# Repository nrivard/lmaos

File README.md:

# LmaOS

LmaOS is a 65C02 system kernal designed primarily for the n8 Bit Microcomputer, a homebrew computer.
If you are looking for the hardware this is designed to run on, check out the [n8 Bit Microcomputer](https://github.com/nrivard/n8-bit).

## Getting Started

To build LmaOS, you will need `make` and the [CC65 suite](https://cc65.github.io) or my unreleased 65C02 IDE for macOS, System On Chip (how did you get this? It's unreleased!)

From the root directory, run `make`:

```bash
$ make
/usr/local/bin/cl65 -t none -C LmaOS.65c02/memorymap.cfg --asm-include-dir LmaOS.65c02/include -l lmaos.rom.listing -vm --mapfile lmaos.rom.map --cpu 65C02 -o ./lmaos.rom  LmaOS.65c02/src/main.asm
```

To install LmaOS on an EEPROM for use in your n8 Bit Microcomputer, you will need [minipro](https://gitlab.com/DavidGriffith/minipro) and a TL866II Plus programmer.
Again, from the root directory, run `make install`:

```bash
$ make install
minipro -p AT28C256 -w lmaos.rom
Found TL866II+ 04.2.122 (0x27a)
Erasing... 0.02Sec OK
Protect off...OK
Writing Code...  6.78Sec  OK
Reading Code...  0.48Sec  OK
```

## Conventions

LmaOS has a few conventions to consider.
First, LmaOS uses 16 bit pseudo-registers for passing data between system subroutines: `r0` through `r7` (see `zeropage.inc`.)
These registers should be considered volatile and if you use them in your program and call system functions, they could be mutated.

Second, register values at this time should _also_ be considered volatile (with the exception of interrupt handling) so if you care about these values, push them onto the stack or store them elsewhere before calling system routines.
Exactly what is used should be in the documentation for each subroutine.

Lastly, some programming conventions are:

* constants and volatile storage (`.bss`) are in an `.inc` file
* code and non-volatile storage (`RODATA`) are in an `.asm` file
* Border-line excessive use of local labels in subroutines (prefixed with `@`).
Not all of these local labels are actually used as labels (in the assembler sense) but instead are intended as self-documenting organizational tools.

For example, many routines will have an immediate local label named `@Preamble` on entry to a subroutine and almost all have a `@Done` before `RTS` even when no branches jump to it.
It's not strictly necessary, you could jump to the top-level label if necessary, but I like to organize the code this way.

```asm
RandomSubroutine:
@Preamble:
    PHA
    PHX
@GenerateRandomNumber:
    ...
@Done:
    PLX
    PLA
    RTS
```

## Hardware Support

LmaOS was written primarily for the n8 Bit Microcomputer but likely needs customization, which could make it suitable for other designs as well.

### System Globals

System globals that are used throughout LmaOS are declared in `system.inc`.
This includes the system clock speed constant (needed for precise timing) and declarations for the n8 Bus ports` addresses.
These follow the default memory mapping of the n8 Bit Microcomputer but you can customize them here if you changed that.

Normally, there should be no need to customize the system uptime interrupt interval unless you need higher accuracy, the routine is taking too much time for your uses, or you want to use it instead as more of a VSYNC timer for consistent frames.

### Zeropage

LmaOS has carved out some of zeropage for particular uses.
This includes the pseudo-registers (which are also for your program use), system uptime, the global interrupt vector, and more.
See `zeropage.inc` for details on what is used and what is available for your own program use.

### Expansion Ports

When you add, remove, or change the order of your installed expansion cards (or your system doesn't have any), you will have to recompile LmaOS.

First you will have to update the base address for system utilities to work.
For example, if you've installed a VIA, in `via.inc` you'll want `VIA_BASE` to point to the correct base memory address.
If you're using a n8 Bit Micrcomputer, you can just use the global n8 Bus port constant:

```asm
VIA_BASE := N8BUS_PORT2
```

There is system support for an ACIA, VIA, and 1602 style LCDs.
If you are using different hardware for these, you may be able to just adapt what is provided for your purposes.

## System utilities

LmaOS provides some system support for the ACIA, VIA, and 1602 style LCDS as well as some built-in strings utilities.

### VIA

The VIA provides system timer support from Timer 1.
If you want to take advantage of system uptime and jiffies, do not use Timer 1 and do not disable interrupts.
By default, both I/O ports are configured for output.
See `via.inc` and `via.asm` for more details.

### ACIA

Basic ACIA functions are provided: `ACIAGetByte`, `ACIASendByte`, and `ACIASendString`.
All of these routines are synchronous, meaning they could lock up the system if there is no response from a connected system.
A fully working interrupt driven ACIA implementation was written if you want to comb the commit history but it was way too complicated for realworld use.
See `acia.inc` and `acia.asm` for more details.

The XModem receive subroutine used by Monitaur's `tx` command is provided for program use as well: `XModemReceive`.
See `xmodem.inc` and `xmodem.asm` for more details.

### Strings

Some C lib like string utilities are provided including: `StringLength`, `StringCompareN`, `StringCompare`, `StringCopy`, `HexStringToWord`, `ByteToHexString`, and `NibbleToHexString`. See `strings.asm` for more details.

### Pseudoinstructions

Pseudoinstructions are provided via macros.
These can simplify common but rote tasks and make your code more readable but be careful when you use them.
They may not always do what you think they do!
You can discover them in `pseudoinstructions.inc`.

## Monitaur

At bootup, LmaOS boots into its monitor, called Monitaur. 
Monitaur provides 4 basic commands: `rd`, `wr`, `tx`, and `ex`.
All numeric values in Monitaur are in hexadecimal (written as `$<number>` throughout this document).
Where noted, a `word` is 16 bits and a `byte` is 8 bits.

In general, Monitaur parses all values as a word but a command may ignore the upper nibble if it expects a byte.
See `monitaur.inc` and `monitaur.asm` for more details.

### Reading memory

The `rd` command allows you to read system memory. You provide an address (word) and, optionally, a length (byte).

```
>rd 0400
A9
```

By default, if you don't specify a length, it defaults to `$1`.
To read blocks of memory, you can provide a length.

```
>rd 1000 10
AB 11 FE 6F D9 DB 2D FD 26 F4 82 FE F1 A6 95 8B
```
 
Monitaur will print `$10` values per line.
Length is provided as a byte and so the maximum value you can read is `$100`. 
To read the full `$100` values, because of how the monitor is written, you must provide the length as `$0` not `$FF`.

```
>rd 1000 0
AB 11 FE 6F D9 DB 2D FD 26 F4 82 FE F1 A6 95 8B 
25 33 49 6F 8D C0 03 3C EA D7 9F F6 0F CB ED E1 
D3 73 F8 4C C7 BA 7F B7 EB 53 5B 5E DD BC FA C1 
63 B7 E8 8F 29 91 A2 5C 13 1B E7 F7 73 72 73 BE 
B1 91 14 FC DA 5A 9F E7 D7 8F CF 7F 82 6E DB F7 
3F E7 AA 9B 1E A8 61 D9 4B 5D FF 9C 58 B7 74 BA 
7C 3D 26 FE 73 77 9F 1E 9B 5F 70 BE 75 AB 37 A3 
45 E4 B5 28 E0 E3 3D C4 D5 F1 9F 60 8F 9C 7E A3 
EE 9E F9 3E EA DF 27 EF F3 55 C8 E8 6D 1A F7 BE 
DA B3 26 C6 FE EE FD 6F 67 58 A7 79 F5 58 B5 4D 
B5 36 FA A8 66 9D B5 91 FF FA 8B B7 FF BF D3 39 
4F E7 F3 BF 39 BF D7 D0 F5 7F FF 9B E8 6C 93 9C 
2C 5C DE DD DD B3 75 7F 3E DE 7B C8 4F 4F 65 EA 
7F E4 5F 51 BF 70 B1 1B FF FF E6 D2 EA F9 77 BD 
93 EE EE 37 51 0F 8B 9E 8F E4 F9 B7 AF CE B7 BB 
FF 13 BE F9 EF FA FF EE ED 27 67 E0 5F BD 11 83
```

### Writing memory

The `wr` command allows you to write to system memory (provided it is writeable!)
You provide an address (word) and a value (byte) to be written.

```
>wr 1000 A5
```

Values can only be written 1 at a time through this command.
There is no feedback if a write fails because you tried to write to an address that is read-only (like ROM).
If you need to know if your `wr` succeeded, send a `rd` command with the address and verify the value.

### Transferring data

The `tx` command allows you to transfer data from the connected system to the n8 Bit Microcomputer.
You provide an address (word) to start writing the data.

```
>tx 0400
Waiting for XModem transfer...
```

When prompted, your connected system can send a file via the XModem Checksum (not CRC) protocol.
When the transfer is completed or canceled, you will be returned to Monitaur.
The `tx` command will write _all_ data sent, including EOF padding (`$1A` from the serial app I use), it makes no attempt to discover the true EOF.

### Executing programs

The `ex` command executes code starting at the provided address (word).

```
>ex 0400
```

`ex` does this by jumping to the provided address as a subroutine (`JSR <address>`).
Your program is expected to know where it will be written (because you likely used `tx` and provided that address!)
When your program is done executing, calling `RTS` will return you to Monitaur.

_Note: You should always start writing your program after address $0400, as there are two `$80` length buffers needed by Monitaur (for command storage) and `tx` (for packet storage) as well as some other bookkeeping when transferring data._

## Writing Programs

The point of the n8 Bit Microcomputer and LmaOS is to write programs and see them come to life!
Take a look at the following guidelines and the included example programs.

### The Basics

To write programs for the n8 Bit Microcomputer (and LmaOS), copy any of the relevant include (`.inc`) files for your use.
Set an origin for your program (I like `$0400`) as there is no built-in relocation scheme yet.
If your program just performs a small task, remember to call `RTS` to return to Monitaur.
If you never need to return to Monitaur, don't worry about it!

_Note: When you transfer your program, the transfer location must match the origin!_

Here's a very simple program that will write an alternating pattern to the VIA's 2 I/O ports:

```asm
.org $0400

Main:
    LDA #$AA
    STA VIA_BASE+PORT_A
    STA VIA_BASE+PORT_B
    RTS

.include "via.inc"
```

Then transfer the program using Monitaur and execute it:

```
LmaOS v1.0
Unauthorized access of this N8 Bit Microcomputer will result in prosecution!
>tx 0400
Waiting for XModem transfer...
Transmission successful.
>ex 0400
>
```

If you need to execute system provided (ROM) subroutines, copy `lmaos.inc` into your project.
This file is not actually used by LmaOS; instead it is just a listing of the addresses of externally available system functionality.

`lmaos.inc` is generated each time you run `make` on LmaOS.
This means you will have to copy this file to your program's project and reassemble each time you update your system's ROM.
You can also directly `include` this file (and all the other system utitilies) as the example programs do in this repo.
See the `Makefile` of the examples for how to do this.

```asm
.org $0400

Main:
@ClearScreen:
    LDA #(LCD_INSTR_CLEAR)
    JSR LCDSendInstruction
@PrintMsg:
    LDA #<WelcomeMsg
    LDX #>WelcomeMsg
    JSR LCDPrintString
@Done:
    RTS

WelcomeMsg: .asciiz "Welcome to LmaOS!"

.include "lmaos.inc"
```

### Injecting Interrupt Handlers

If you add new hardware support or want to piggyback on the system timer interrupt, LmaOS provides a way to inject your own interrupt handlers.

First, you will need to overwrite `InterruptVector` (we will write `CustomInterrupt` in the next step):

```asm
SystemInterrupt: .res 2                         ; we'll store the original vector here

InjectInterrupt:
    SEI                                         ; turn off interrupts. we don't want them firing when we overwrite this
    COPY16 InterruptVector, SystemInterrupt     ; store original vector
    COPYADDR CustomInterrupt, InterruptVector   ; inject our interrupt
    CLI                                         ; turn interrupts back on
```

A couple notes about injecting your subroutine:

* as noted in the code, make sure you turn _off_ interrupts before overwriting this value, otherwise you could jump to a random part of memory if an interrupt occurs in the middle of this operation
* be sure to store the value of the current system interrupt handler.
You never know who is actually invoking your program and they may have set up their own custom handler.
* when you're done, turn interrupts back _on_.

Next, write your custom interrupt handler:

```asm
CustomInterruptHandler:
    BIT N8BUS_PORT_1                   ; test our custom hardware to see if this interrupt is intended for us :)
    BPL @Unhandled                     ; in this scenario highest-order bit set means we should handle it
@HandleInterrupt:
    PHA
    PHX
    ;; now do our work as quickly as possible!
    PLX
    PLA
    RTI                                ; return directly. if other interrupts are present they'll get handled :)
@Unhandled:
    JMP (SystemInterrupt)              ; let the system handle it
```

A couple notes about this handler:

* if you have fully handled the interrupt, call `RTI`.
Even if there is a system timer event at the same time, it will re-raise the interrupt.
* if you didn't handle the interrupt (because your hardware didn't raise it, for example), `JMP` to `InterruptHandleSystemTimer`, the declared system interrupt handler.
That will call `RTI` for you when it's finished.
* Be a good system citizen!
Be as fast as you can and preserve any register values before either calling `RTI` or jumping to the system interrupt handler.

When your program is done and you want to return to Monitaur, you need to set the interrupt back to its original value.
Like before, make sure you're only editing the system's interrupt handler when interrupts are _off_.

```asm
RestoreInterrupt:
    SEI
    COPY16 SystemInterrupt, InterruptVector
    CLI
```

## Future Support

Planned improvements for LmaOS include:

* FAT filesystem support
* bootstrapping Monitaur and other system utilities from FAT storage
* OLED display routines
* standalone input (keyboard, controller, etc.)
* DUART support

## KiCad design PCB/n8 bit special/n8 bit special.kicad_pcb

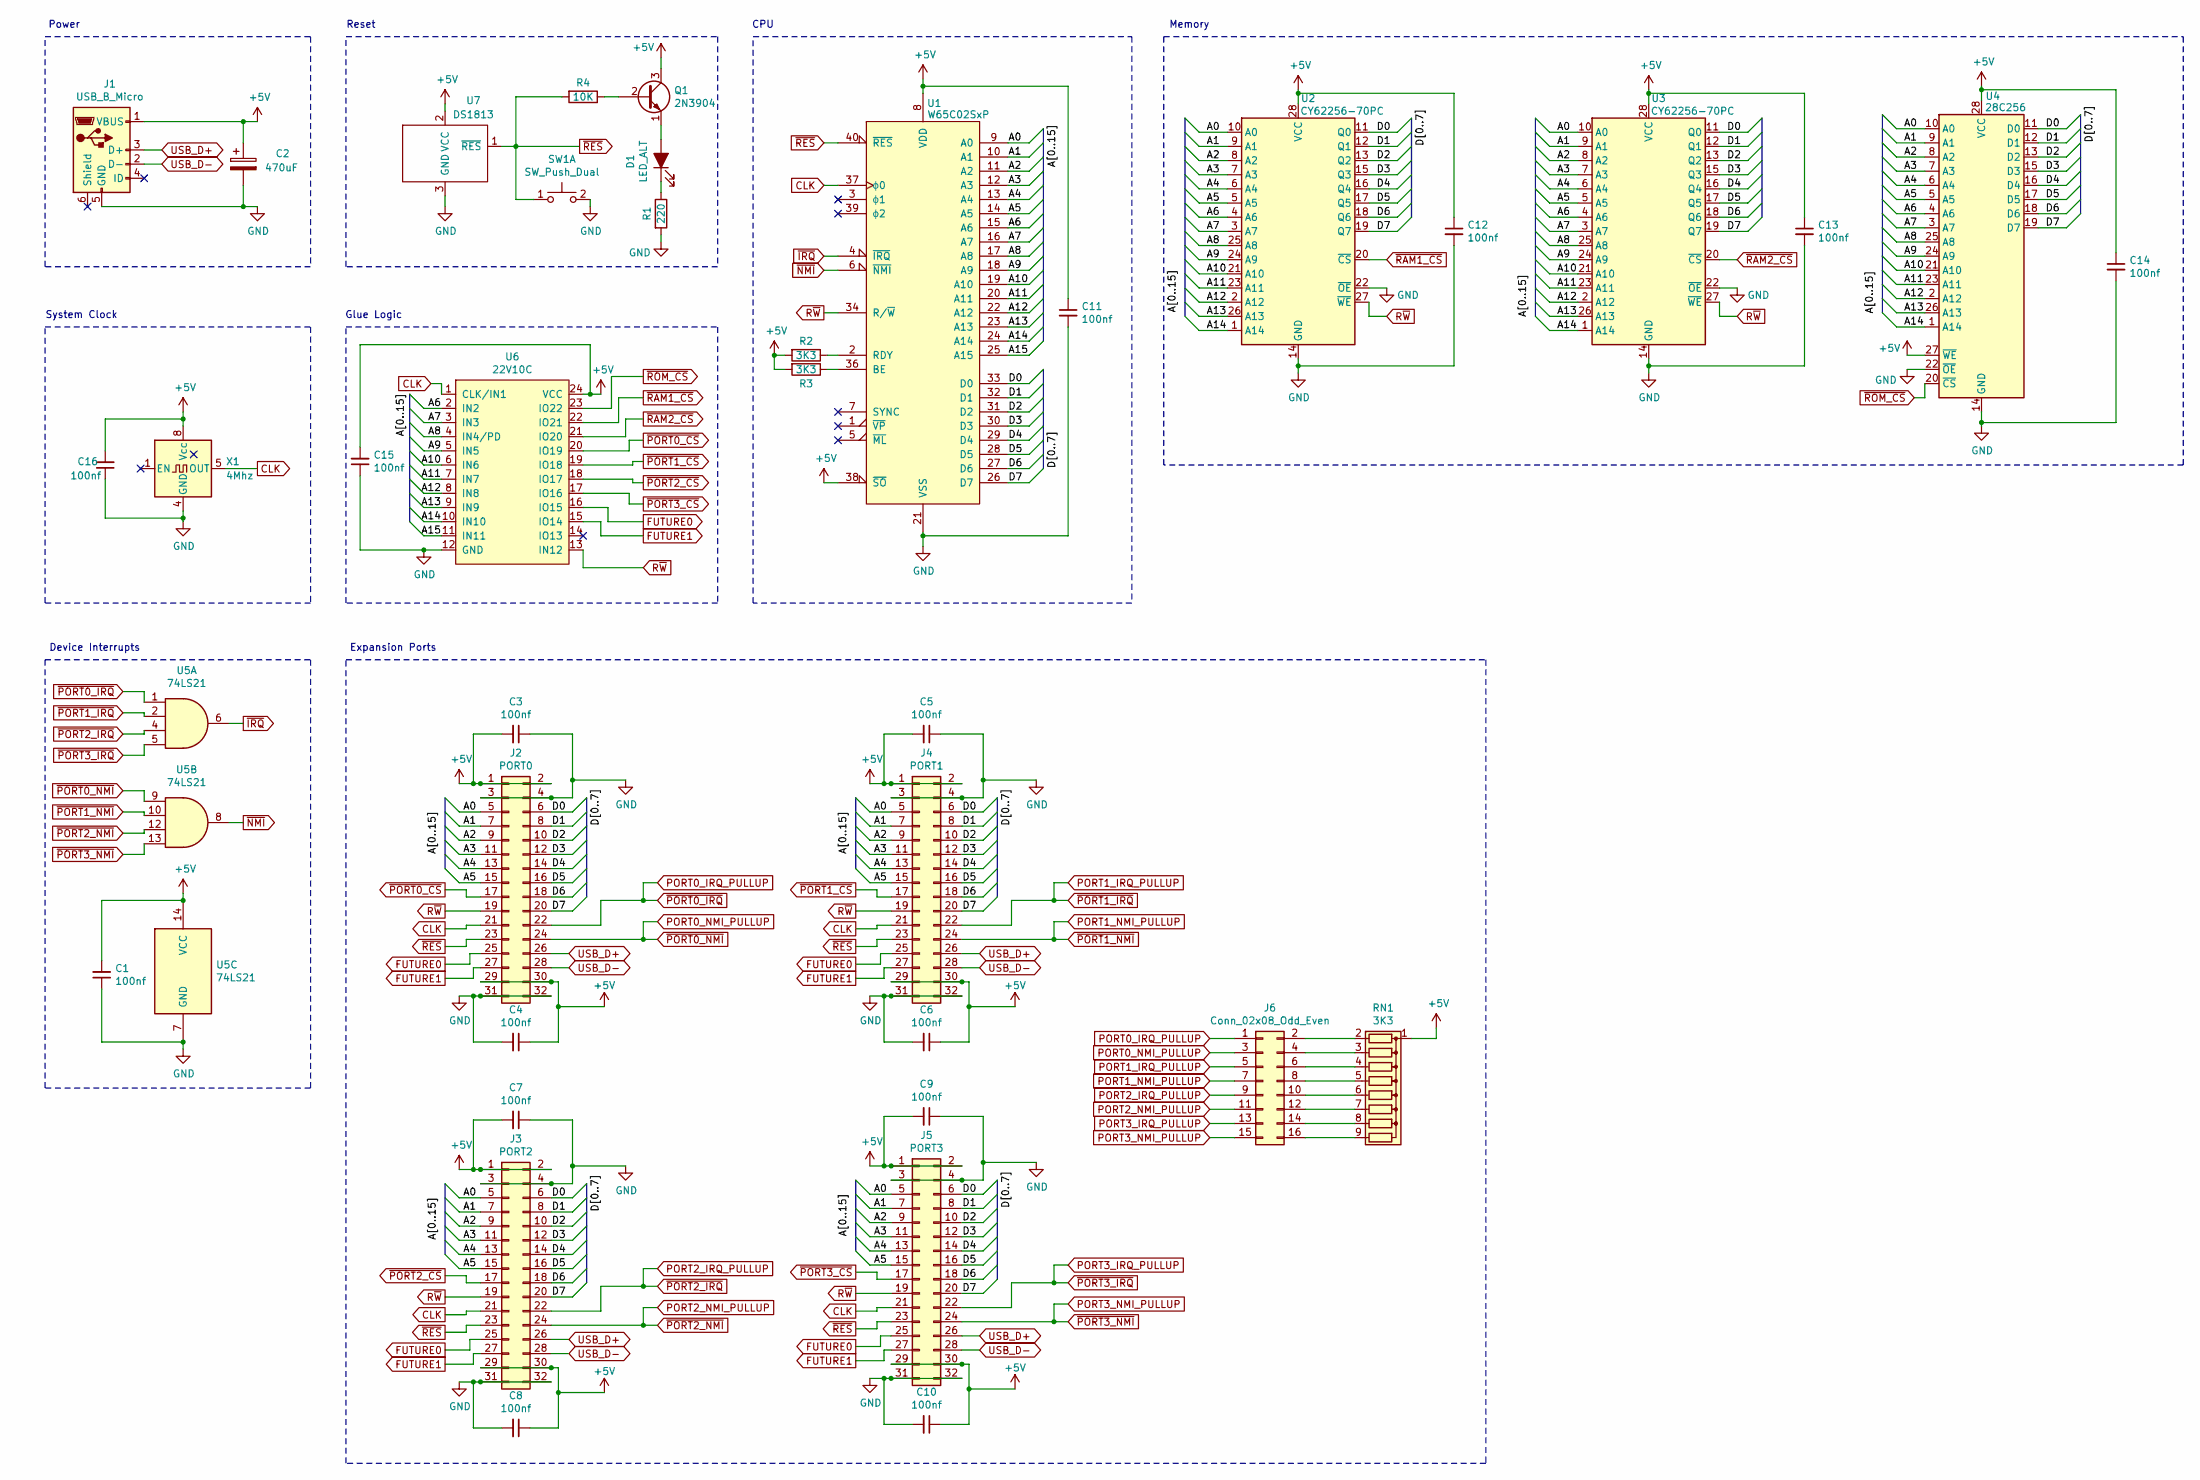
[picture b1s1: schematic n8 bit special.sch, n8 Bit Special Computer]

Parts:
C1, C3, C4, C5, C6, C7, C8, C9, C10, C11, C12, C13, C14, C15, C16: 100nf; C_Disc_D5.0mm_W2.5mm_P2.50mm
C2: 470uF; CP_Radial_D8.0mm_P3.80mm
D1: LED_ALT; LED_D3.0mm
J1: USB_B_Micro; USB_Micro-B_Amphenol_10118194_Horizontal
J2: PORT0; PinSocket_2x16_P2.54mm_Vertical
J3: PORT2; PinSocket_2x16_P2.54mm_Vertical
J4: PORT1; PinSocket_2x16_P2.54mm_Vertical
J5: PORT3; PinSocket_2x16_P2.54mm_Vertical
J6: Conn_02x08_Odd_Even; PinHeader_2x08_P2.54mm_Vertical
Q1: 2N3904; TO-92
R1: 220; R_Axial_DIN0207_L6.3mm_D2.5mm_P7.62mm_Horizontal
R2, R3: 3K3; R_Axial_DIN0207_L6.3mm_D2.5mm_P7.62mm_Horizontal
R4: 10K; R_Axial_DIN0207_L6.3mm_D2.5mm_P7.62mm_Horizontal
RN1: 3K3; R_Array_SIP9
SW1: SW_Push_Dual; SW_PUSH_6mm
U1: W65C02SxP; DIP-40_W15.24mm_Socket
U2, U3: CY62256-70PC; DIP-28_W15.24mm_Socket
U4: 28C256; DIP-28_W15.24mm_Socket
U5: 74LS21; DIP-14_W7.62mm_Socket
U6: 22V10C; DIP-24_W7.62mm_Socket
U7: DS1813; TO-92; MANUFACTURER_PART_NUMBER ds181315+
X1: 4Mhz; Oscillator_DIP-8

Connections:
+5V: C1.2, C2.1, C3.2, C4.1, C5.2, C6.1, C7.2, C8.1, C9.2, C10.1, C11.1, C12.1, C13.1, C14.1, C15.2, C16.2, J1.1 (VBUS), J2.1, J2.2, J2.29, J2.30, J3.1, J3.2, J3.29, J3.30, J4.1, J4.2, J4.29, J4.30, J5.1, J5.2, J5.29, J5.30, Q1.3 (C), R2.2, R3.2, RN1.1 (common), U1.8 (VDD), U1.38 (~SO), U2.28 (VCC), U3.28 (VCC), U4.27 (~WE), U4.28 (VCC), U5.14 (VCC), U6.24 (VCC), U7.2 (VCC), X1.8 (Vcc)
/A0: J2.5, J3.5, J4.5, J5.5, U1.9 (A0), U2.10 (A0), U3.10 (A0), U4.10 (A0)
/A1: J2.7, J3.7, J4.7, J5.7, U1.10 (A1), U2.9 (A1), U3.9 (A1), U4.9 (A1)
/A2: J2.9, J3.9, J4.9, J5.9, U1.11 (A2), U2.8 (A2), U3.8 (A2), U4.8 (A2)
/A3: J2.11, J3.11, J4.11, J5.11, U1.12 (A3), U2.7 (A3), U3.7 (A3), U4.7 (A3)
/A4: J2.13, J3.13, J4.13, J5.13, U1.13 (A4), U2.6 (A4), U3.6 (A4), U4.6 (A4)
/A5: J2.15, J3.15, J4.15, J5.15, U1.14 (A5), U2.5 (A5), U3.5 (A5), U4.5 (A5)
/A6: U1.15 (A6), U2.4 (A6), U3.4 (A6), U4.4 (A6), U6.2 (IN2)
/A7: U1.16 (A7), U2.3 (A7), U3.3 (A7), U4.3 (A7), U6.3 (IN3)
/A8: U1.17 (A8), U2.25 (A8), U3.25 (A8), U4.25 (A8), U6.4 (IN4/PD)
/A9: U1.18 (A9), U2.24 (A9), U3.24 (A9), U4.24 (A9), U6.5 (IN5)
/A10: U1.19 (A10), U2.21 (A10), U3.21 (A10), U4.21 (A10), U6.6 (IN6)
/A11: U1.20 (A11), U2.23 (A11), U3.23 (A11), U4.23 (A11), U6.7 (IN7)
/A12: U1.22 (A12), U2.2 (A12), U3.2 (A12), U4.2 (A12), U6.8 (IN8)
/A13: U1.23 (A13), U2.26 (A13), U3.26 (A13), U4.26 (A13), U6.9 (IN9)
/A14: U1.24 (A14), U2.1 (A14), U3.1 (A14), U4.1 (A14), U6.10 (IN10)
/A15: U1.25 (A15), U6.11 (IN11)
/D0: J2.6, J3.6, J4.6, J5.6, U1.33 (D0), U2.11 (Q0), U3.11 (Q0), U4.11 (D0)
/D1: J2.8, J3.8, J4.8, J5.8, U1.32 (D1), U2.12 (Q1), U3.12 (Q1), U4.12 (D1)
/D2: J2.10, J3.10, J4.10, J5.10, U1.31 (D2), U2.13 (Q2), U3.13 (Q2), U4.13 (D2)
/D3: J2.12, J3.12, J4.12, J5.12, U1.30 (D3), U2.15 (Q3), U3.15 (Q3), U4.15 (D3)
/D4: J2.14, J3.14, J4.14, J5.14, U1.29 (D4), U2.16 (Q4), U3.16 (Q4), U4.16 (D4)
/D5: J2.16, J3.16, J4.16, J5.16, U1.28 (D5), U2.17 (Q5), U3.17 (Q5), U4.17 (D5)
/D6: J2.18, J3.18, J4.18, J5.18, U1.27 (D6), U2.18 (Q6), U3.18 (Q6), U4.18 (D6)
/D7: J2.20, J3.20, J4.20, J5.20, U1.26 (D7), U2.19 (Q7), U3.19 (Q7), U4.19 (D7)
CLK: J2.21, J3.21, J4.21, J5.21, U1.37 (ϕ0), U6.1 (CLK/IN1), X1.5 (OUT)
FUTURE0: J2.25, J3.25, J4.25, J5.25, U6.16 (IO15)
FUTURE1: J2.27, J3.27, J4.27, J5.27, U6.15 (IO14)
GND: C1.1, C2.2, C3.1, C4.2, C5.1, C6.2, C7.1, C8.2, C9.1, C10.2, C11.2, C12.2, C13.2, C14.2, C15.1, C16.1, J1.5 (GND), J2.3, J2.4, J2.31, J2.32, J3.3, J3.4, J3.31, J3.32, J4.3, J4.4, J4.31, J4.32, J5.3, J5.4, J5.31, J5.32, R1.2, SW1.2 (D), U1.21 (VSS), U2.14 (GND), U2.22 (~OE), U3.14 (GND), U3.22 (~OE), U4.14 (GND), U4.22 (~OE), U5.7 (GND), U6.12 (GND), U7.3 (GND), X1.4 (GND)
unnamed: D1.1 (K), R1.1
unnamed: D1.2 (A), Q1.1 (E)
unnamed: J6.2, RN1.2 (R1)
unnamed: J6.4, RN1.3 (R2)
unnamed: J6.6, RN1.4 (R3)
unnamed: J6.8, RN1.5 (R4)
unnamed: J6.10, RN1.6 (R5)
unnamed: J6.12, RN1.7 (R6)
unnamed: J6.14, RN1.8 (R7)
unnamed: J6.16, RN1.9 (R8)
unnamed: Q1.2 (B), R4.1
unnamed: R2.1, U1.2 (RDY)
unnamed: R3.1, U1.36 (BE)
PORT0_IRQ_PULLUP: J2.22, J6.1, U5.1
PORT0_NMI_PULLUP: J2.24, J6.3, U5.9
PORT1_IRQ_PULLUP: J4.22, J6.5, U5.2
PORT1_NMI_PULLUP: J4.24, J6.7, U5.10
PORT2_IRQ_PULLUP: J3.22, J6.9, U5.4
PORT2_NMI_PULLUP: J3.24, J6.11, U5.12
PORT3_IRQ_PULLUP: J5.22, J6.13, U5.5
PORT3_NMI_PULLUP: J5.24, J6.15, U5.13
R~W: J2.19, J3.19, J4.19, J5.19, U1.34 (R/~W), U2.27 (~WE), U3.27 (~WE), U6.13 (IN12)
USB_D+: J1.3 (D+), J2.26, J3.26, J4.26, J5.26
USB_D-: J1.2 (D-), J2.28, J3.28, J4.28, J5.28
~IRQ: U1.4 (~IRQ), U5.6
~NMI: U1.6 (~NMI), U5.8
~PORT0_CS: J2.17, U6.20 (IO19)
~PORT1_CS: J4.17, U6.19 (IO18)
~PORT2_CS: J3.17, U6.18 (IO17)
~PORT3_CS: J5.17, U6.17 (IO16)
~RAM1_CS: U2.20 (~CS), U6.22 (IO21)
~RAM2_CS: U3.20 (~CS), U6.21 (IO20)
~RES: J2.23, J3.23, J4.23, J5.23, R4.2, SW1.1 (C), U1.40 (~RES), U7.1 (~RES)
~ROM_CS: U4.20 (~CS), U6.23 (IO22)

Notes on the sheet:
Device Interrupts
Memory
CPU
Glue Logic
Reset
System Clock
Expansion Ports
Power

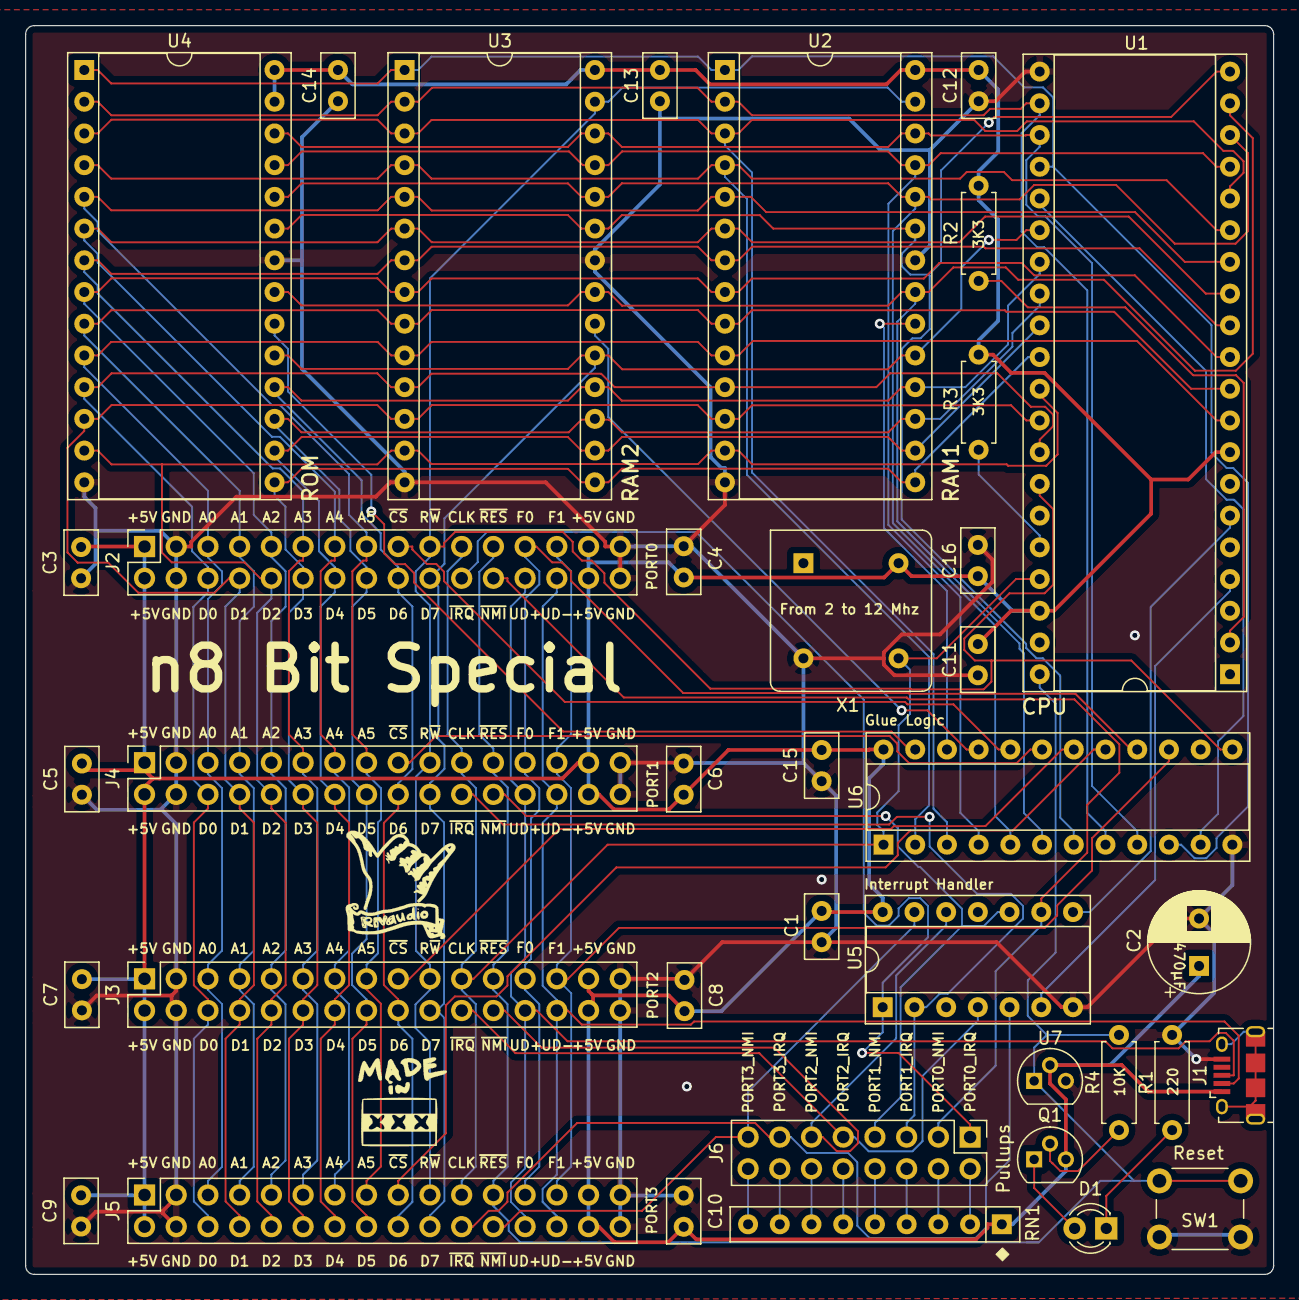
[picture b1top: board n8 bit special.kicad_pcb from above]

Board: 2 copper layers, 99.9 x 100.0 mm, 38 parts (0 on the bottom side), 63 nets.

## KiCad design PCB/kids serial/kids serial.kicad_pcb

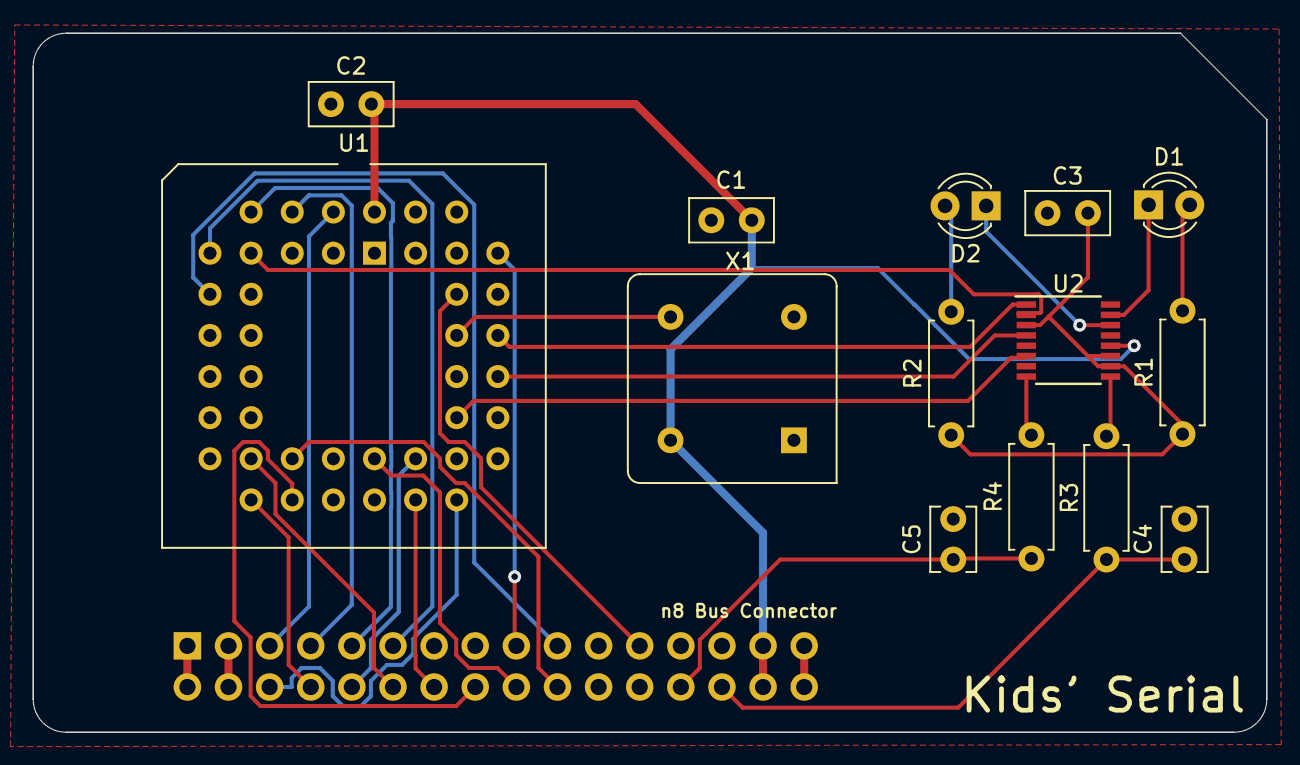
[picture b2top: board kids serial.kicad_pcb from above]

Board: 2 copper layers, 76.2 x 43.2 mm, 15 parts (1 on the bottom side), 32 nets.

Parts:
C1, C2, C3: 100nF; C_Disc_D5.0mm_W2.5mm_P2.50mm
C4, C5: 47pF; C_Disc_D3.8mm_W2.6mm_P2.50mm
D1: TX; LED_D3.0mm
D2: RX; LED_D3.0mm
J1: n8 Bus Connector; PinHeader_2x16_P2.54mm_Horizontal
R1, R2: 330; R_Axial_DIN0207_L6.3mm_D2.5mm_P7.62mm_Horizontal
R3, R4: 27; R_Axial_DIN0207_L6.3mm_D2.5mm_P7.62mm_Horizontal
U1: SC28L92_PLC44; PLCC-44_THT-Socket
U2: FT230XS; SSOP-16_3.9x4.9mm_P0.635mm
X1: 3.6864Mhz; Oscillator_DIP-8

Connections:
+3V3: C3.1, R1.1, R2.1, U2.3, U2.10, U2.11
+5V: C1.1, C2.1, J1.1, J1.2, J1.29, J1.30, U1.44, U2.12, X1.8
/A0: J1.5, U1.2
/A1: J1.7, U1.4
/A2: J1.9, U1.6
/A3: J1.11, U1.7
/D0: J1.6, U1.28
/D1: J1.8, U1.18
/D2: J1.10, U1.27
/D3: J1.12, U1.19
/D4: J1.14, U1.26
/D5: J1.16, U1.20
/D6: J1.18, U1.25
/D7: J1.20, U1.21
GND: C1.2, C2.2, C3.2, C4.2, C5.2, J1.3, J1.4, J1.31, J1.32, U1.12, U1.22, U2.5, U2.13, X1.4
unnamed: D1.1, U2.15
unnamed: D1.2, R1.2
unnamed: D2.1, U2.14
unnamed: D2.2, R2.2
unnamed: R3.1, U2.9
unnamed: R4.1, U2.8
RxD: U1.35, U2.1
R~W: J1.19, U1.9
TxD: U1.33, U2.4
USB_D+: C5.1, J1.26, R4.2
USB_D-: C4.1, J1.28, R3.2
XTAL_CLK: U1.36, X1.5
~CS: J1.17, U1.39
~CTS: U1.8, U2.2
~IRQ: J1.22, U1.24
~RES: J1.23, U1.38
~RTS: U1.32, U2.6

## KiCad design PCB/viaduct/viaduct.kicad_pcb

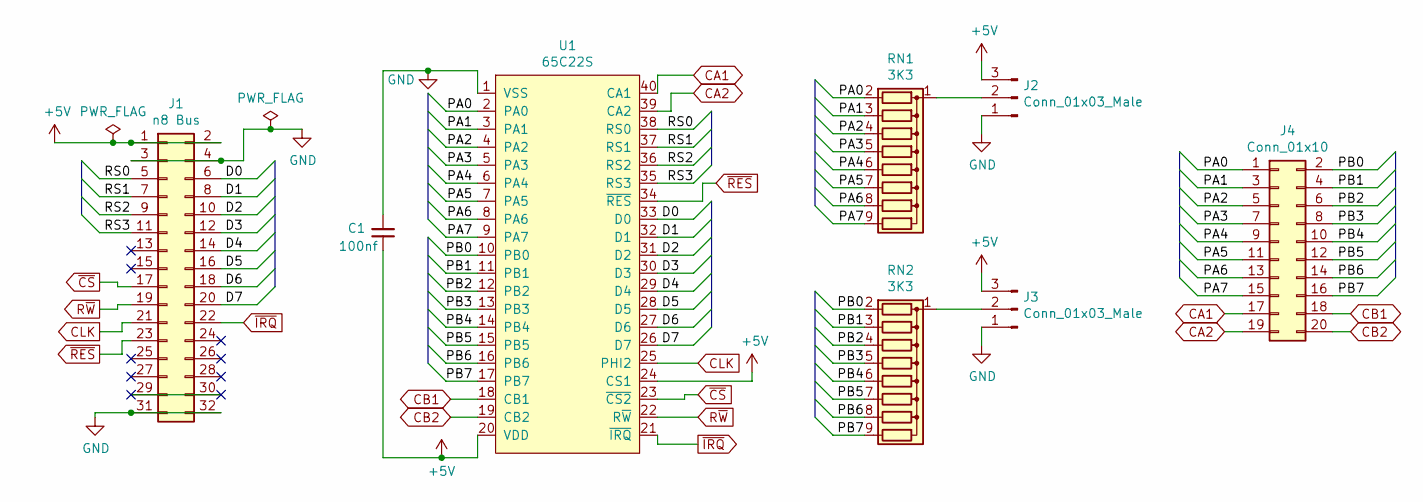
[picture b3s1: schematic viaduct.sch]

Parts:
C1: 100nf; C_Disc_D5.0mm_W2.5mm_P2.50mm
J1: n8 Bus; PinHeader_2x16_P2.54mm_Horizontal
J2, J3: Conn_01x03_Male; PinHeader_1x03_P2.54mm_Vertical
J4: Conn_01x10; PinSocket_2x10_P2.54mm_Horizontal
RN1, RN2: 3K3; R_Array_SIP9
U1: 65C22S; DIP-40_W15.24mm_Socket

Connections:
+5V: C1.1, J1.1, J1.2, J2.3, J3.3, U1.20 (VDD), U1.24 (CS1)
/D0: J1.6, U1.33 (D0)
/D1: J1.8, U1.32 (D1)
/D2: J1.10, U1.31 (D2)
/D3: J1.12, U1.30 (D3)
/D4: J1.14, U1.29 (D4)
/D5: J1.16, U1.28 (D5)
/D6: J1.18, U1.27 (D6)
/D7: J1.20, U1.26 (D7)
/PA0: J4.1, RN1.2 (R1), U1.2 (PA0)
/PA1: J4.3, RN1.3 (R2), U1.3 (PA1)
/PA2: J4.5, RN1.4 (R3), U1.4 (PA2)
/PA3: J4.7, RN1.5 (R4), U1.5 (PA3)
/PA4: J4.9, RN1.6 (R5), U1.6 (PA4)
/PA5: J4.11, RN1.7 (R6), U1.7 (PA5)
/PA6: J4.13, RN1.8 (R7), U1.8 (PA6)
/PA7: J4.15, RN1.9 (R8), U1.9 (PA7)
/PB0: J4.2, RN2.2 (R1), U1.10 (PB0)
/PB1: J4.4, RN2.3 (R2), U1.11 (PB1)
/PB2: J4.6, RN2.4 (R3), U1.12 (PB2)
/PB3: J4.8, RN2.5 (R4), U1.13 (PB3)
/PB4: J4.10, RN2.6 (R5), U1.14 (PB4)
/PB5: J4.12, RN2.7 (R6), U1.15 (PB5)
/PB6: J4.14, RN2.8 (R7), U1.16 (PB6)
/PB7: J4.16, RN2.9 (R8), U1.17 (PB7)
/RS0: J1.5, U1.38 (RS0)
/RS1: J1.7, U1.37 (RS1)
/RS2: J1.9, U1.36 (RS2)
/RS3: J1.11, U1.35 (RS3)
CA1: J4.17, U1.40 (CA1)
CA2: J4.19, U1.39 (CA2)
CB1: J4.18, U1.18 (CB1)
CB2: J4.20, U1.19 (CB2)
CLK: J1.21, U1.25 (PHI2)
GND: C1.2, J1.3, J1.4, J1.31, J1.32, J2.1, J3.1, U1.1 (VSS)
unnamed: J1.29, J1.30
unnamed: J2.2, RN1.1 (common)
unnamed: J3.2, RN2.1 (common)
R~W: J1.19, U1.22 (R~W)
~CS: J1.17, U1.23 (~CS2)
~IRQ: J1.22, U1.21 (~IRQ)
~RES: J1.23, U1.34 (~RES)

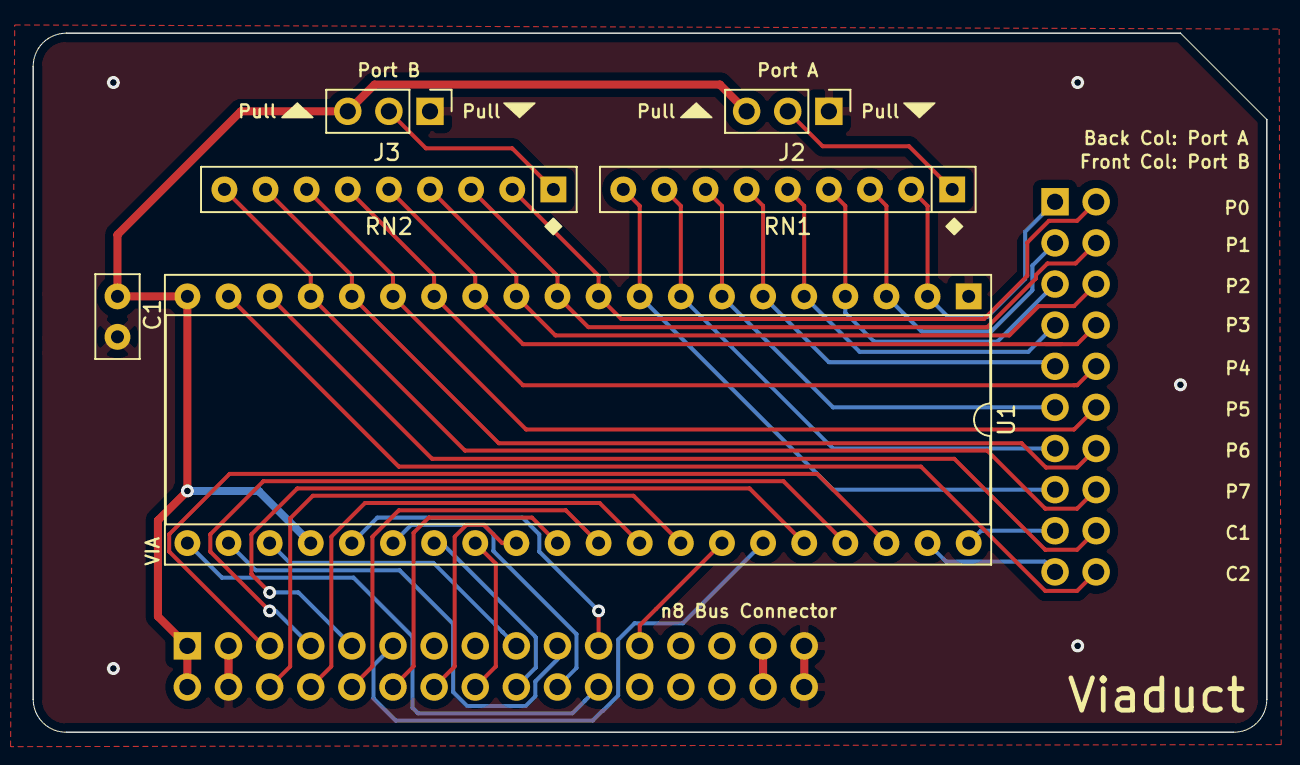
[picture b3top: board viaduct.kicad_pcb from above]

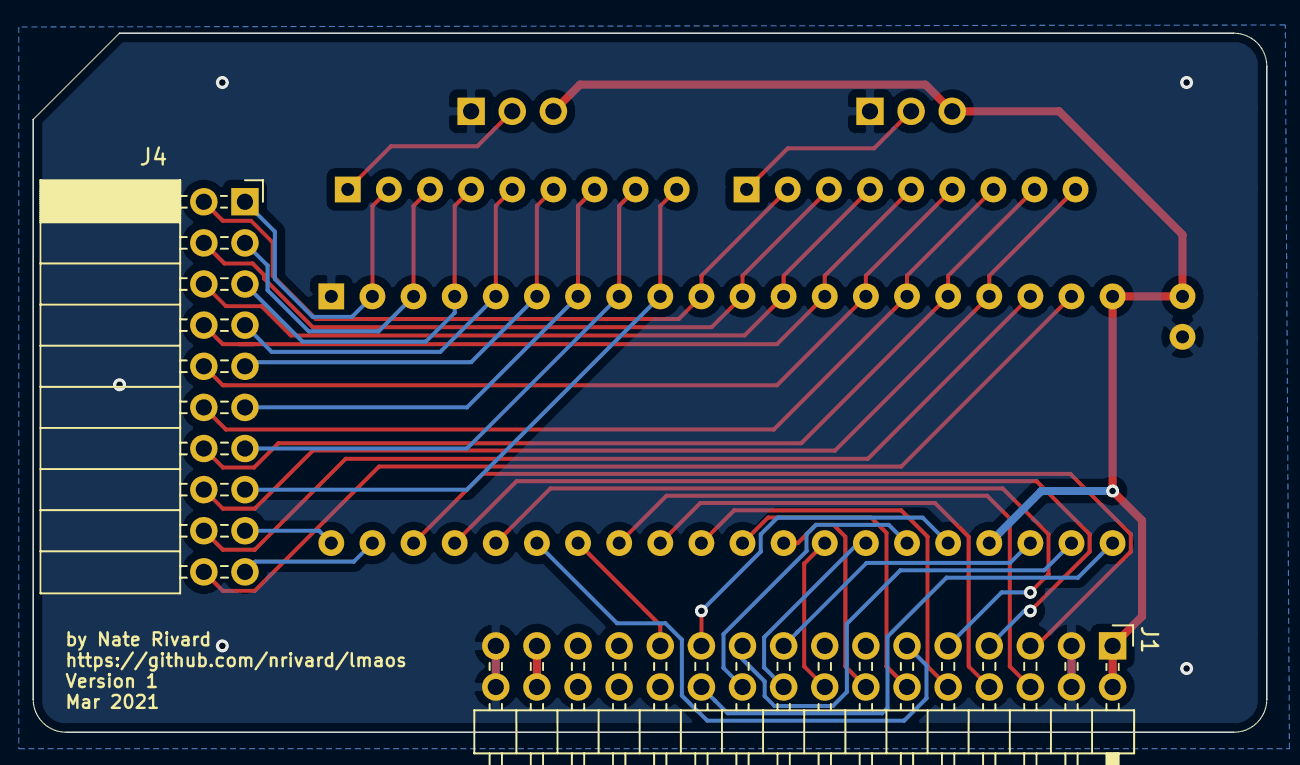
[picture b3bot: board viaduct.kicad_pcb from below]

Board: 2 copper layers, 76.2 x 43.2 mm, 8 parts (2 on the bottom side), 42 nets.

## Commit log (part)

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2020-12-20 Added System On Chip project
2021-01-08 Latest state of async monitor
2021-01-11 working `rd` command!
2021-02-09 Started adding vscode support
2021-02-10 Failing Makefile but want to preserve changes just in case
2021-02-10 Modern complex project setup.
2021-02-15 Rewrote the monitor (and renamed it)
2021-02-16 Cleanup
2021-02-16 Start of XModem transfers
2021-02-17 Non-working implementation of XModem
    Checking this in for comparison purposes but this does not implement Xmodem correctly because this can nack in the middle of packet transmission. I believe I need to check for <SOH> (vs. <EOT>) and i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
2021-02-19 Working xmodem implementation!
2021-02-19 Added image of the computer and fleshed out README
2021-02-19 Updated readme and fixed image issue
2021-02-19 Updated readme and added more documentation
2021-02-19 Fixed typos and readability
2021-02-23 Added 1602a LCD functionality
2021-02-24 Started adding sample projects
2021-02-24 Added more to README and fixed address decoder bug
2021-03-03 working animated "game"
2021-03-04 Start of a PCB and schematic
2021-03-04 Fixed some issues with output enable connections
2021-03-08 Start of PCB layout
2021-03-08 Near final board
2021-03-09 Added production gerbers
2021-03-10 Added WinCUPL files wholesale
    This changes the address decoding to match the PCB layout.
    0000...7FFF RAM1
    8000...BEFF RAM2
    BF00...BF3F PORT0
    BF40...BF7F PORT1
    BF80...BFBF PORT2
2021-03-12 Start of the Viaduct
    Viaduct is a GPIO expansion card using a 65C22S.
2021-03-12 asdf
2021-03-13 Close to final Viaduct and Kids' Serial cards
2021-03-13 Added more documentation for the expansion cards
2021-03-13 Last commit for v1
2021-03-16 version 2 of the PCB
2021-03-17 Start of Kids' Serial v2
2021-03-24 Nearly final v2 PCBs
2021-03-25 v2 of the n8 bit special
2021-03-27 v2 done
2021-04-01 More v2 changes
2021-05-25 Working kernal for v1 of the board
2021-06-03 working acia test
2021-06-04 Xmodem transfers working!
2021-06-07 fixed bugs and added debug flag for tokenization
2021-08-12 Created an example program to test v1 hardware
2022-02-01 Removed hardware
    Removed hardware which is now in its own repo. This includes the `PCB`, `GlueLogic`, and `logs` folders.
    Also fixed a bug in the Fibonacci example program.
    Lastly, changed some locations for my hardware, but you should edit these for your own setup anyway.
2022-02-02 README typo fix
2022-02-02 Generating `lmaos.inc` now
    Doing somewhat rudimentary generation of the system globals but it's much better than hand writing it!
2022-02-02 Updated .gitignore
2022-02-02 Added a new example program showing how to inject a custom interrupt handler
2022-02-03 Doc update to mention example programs
2022-02-03 Fixed potential issue if there are an odd number of exports
2022-02-03 Converted tabs (ahh!) to spaces (phew!)
2022-02-03 Removed hardware related pictures
2022-02-13 Start of an SD Card lib
2022-02-14 Fully initializes and verifies high capacity cards
2022-02-22 Working SPI, SD card commands, and start of Fat32 lib
2022-04-22 Added SDCard example
2022-05-31 Reading files and directories (only in root)
2022-06-02 Reads file location and size and prints it in a table
2022-08-01 Changes for v2 of n8 bit hardware, notably, removal of PORT3
2022-08-05 More fixes for new SC28L92 hardware
    Added Duart driver files, added abstract Serial* functions that can point to either duart or expansion ACIA, converted all kernel usage of ACIA* to Serial*, fixed up example programs, changed system 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
2022-08-08 Small updates
2022-08-09 Remove VIA from system ROM. User's can initialize the card how they want
2022-08-09 Removed LCD references from main rom bootup
2022-08-09 Changes in prep for following FAT chains
2023-03-21 Start of VDP support
2023-03-27 working "shell" example
2023-03-28 Added a new game: Inv8ers
2023-03-30 working sprite movement
2023-04-06 2 working programs now
2023-05-10 moved vdp routines to ROM and started a new tech demo
2023-07-03 Added new example
2023-07-07 Closer...
2023-09-18 Start of Yamahawk
2023-11-07 Added BASIC!
2025-07-02 vdp tests
2025-07-12 work
